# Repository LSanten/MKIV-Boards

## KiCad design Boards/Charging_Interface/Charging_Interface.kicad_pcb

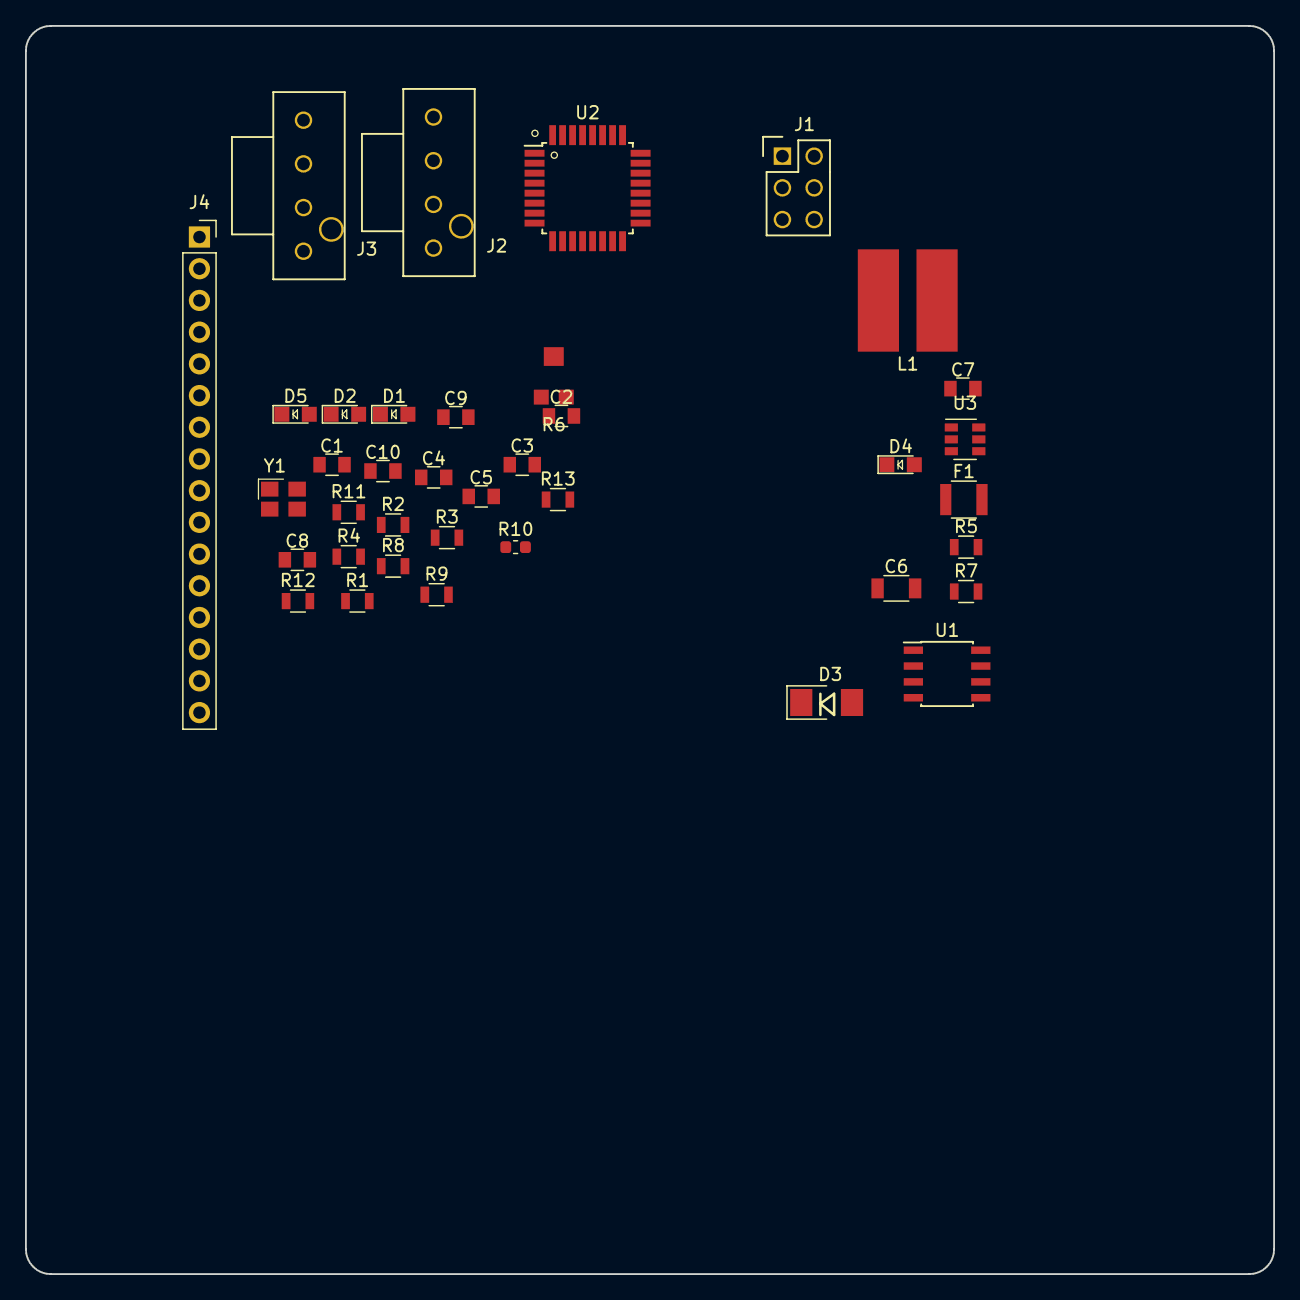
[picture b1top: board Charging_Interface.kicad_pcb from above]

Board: 2 copper layers, 100.0 x 100.0 mm, 38 parts (0 on the bottom side), 41 nets, no tracks yet.

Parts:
C1, C3, C7, C8: C_0.1uF; C_0805_OEM
C2: C_100pF; C_0805_OEM
C4, C5: C_30pF; C_0805_OEM
C6: C_22uF; C_1206_OEM
C9: C_1uF; C_0805_OEM
C10: C_47uF; C_0805_OEM
D1, D2, D4, D5: LED_0805; LED_0805_OEM
D3: D_Zener_18V; DO-214AA
F1: F_500mA_16V; Fuse_1210
J1: CONN_02X03; Pin_Header_Straight_2x03
J2, J3: UF_4_VT; Ultrafit_4
J4: 0.1in_Female_Socket_01x16; PinSocket_1x16_P2.54mm_Vertical
L1: L_4.7uH; 4.7uH_Inductor_OEM
R1, R13: R_100; R_0805_OEM
R2, R3, R11: R_200; R_0805_OEM
R4, R7, R8: R_10K; R_0805_OEM
R5: R_1K; R_0805_OEM
R6: POT_TRIM_20k
R9: R_51.1K; R_0805_OEM
R10: R_0; R_0603_1608Metric
R12: R_120; R_0805_OEM
U1: MCP2561-E_SN; SOIC-8_3.9x4.9mm_Pitch1.27mm_OEM
U2: ATMEGA16M1; TQFP-32_7x7mm_Pitch0.8mm
U3: TPS561201; SOT-23-6_OEM
Y1: Crystal_SMD; Crystal_SMD_FA238

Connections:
+5V: C1.1, C3.1, J1.2, J4.2, R1.1, R4.1, R6.1, R10.1, R11.1, R13.2, U1.3, U2.4
+12V: D3.1, F1.1, J2.1
/AMS: J3.3, U2.15
/CANH: J2.3, R12.1, U1.7
/CANL: J2.4, R12.2, U1.6
/DB0: J4.7, U2.8
/DB1: J4.8, U2.9
/DB2: J4.9, U2.16
/DB3: J4.10, U2.23
/DB4: J4.11, U2.24
/DB5: J4.12, U2.26
/DB6: J4.13, U2.27
/DB7: J4.14, U2.28
/E: J4.6, U2.29
/IMD: J3.1, U2.14
/MISO: J1.1, U2.1
/MOSI: J1.4, U2.2
/RESET: J1.5, R4.2, U2.31
/RS: J4.4, U2.32
/RXCAN: U1.4, U2.7
/R_W: J4.5, U2.30
/SCK: J1.3, U2.12
/TXCAN: U1.1, U2.6
GND: C1.2, C2.2, C3.2, C4.2, C5.2, C6.2, C8.2, C9.2, C10.2, D1.1, D2.1, D3.2, D4.1, D5.1, J1.6, J2.2, J3.2, J3.4, J4.1, J4.16, R6.3, R8.2, U1.2, U1.8, U2.5, U2.20, U3.1, Y1.2, Y1.4
unnamed: C2.1, R1.2, U2.19
unnamed: C4.1, U2.11, Y1.1
unnamed: C5.1, U2.10, Y1.3
unnamed: C6.1, F1.2, R5.2, R7.2, U3.3
unnamed: C7.1, U3.6
unnamed: C7.2, L1.1, U3.2
unnamed: C8.1, C9.1, C10.1, L1.2, R9.1, R10.2
unnamed: D1.2, R2.1
unnamed: D2.2, R3.1
unnamed: D4.2, R5.1
unnamed: D5.2, R11.2
unnamed: J4.3, R6.2
unnamed: J4.15, R13.1
unnamed: R2.2, U2.22
unnamed: R3.2, U2.25
unnamed: R7.1, U3.5
unnamed: R8.1, R9.2, U3.4

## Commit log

2018-11-13 Schematic almost finished
    CANH/CANL doesn't have connector at the moment
    Pot trim symbol isn't in formula library
2018-12-05 started layour for charging interface
